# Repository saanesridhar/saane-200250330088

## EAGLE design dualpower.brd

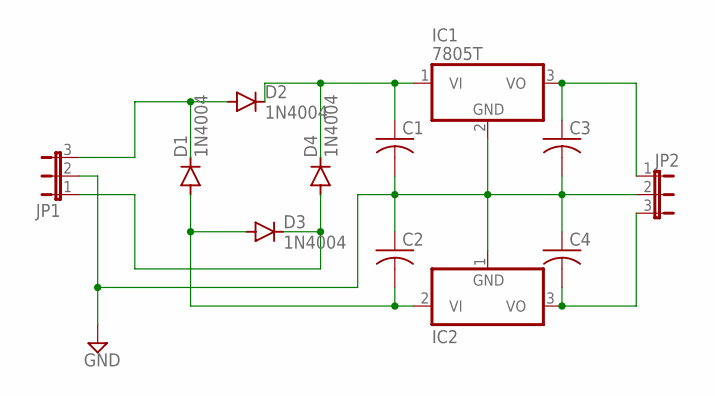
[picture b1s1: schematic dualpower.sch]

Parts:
C1, C2, C3, C4: C-US025-024X044; C025-024X044
D1, D2, D3, D4: 1N4004; DO41-10
IC1: 7805T; TO220H
IC2: 79L05Z; TO92
JP1, JP2: JP2W

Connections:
GND: C1.2, C2.1, C3.2, C4.1, IC1.2 (GND), IC2.1 (GND), JP1.2, JP2.2
unnamed: D1.C, D2.A, JP1.3
unnamed: C2.2, D1.A, D3.A, IC2.2 (VI)
unnamed: D3.C, D4.A, JP1.1
unnamed: C1.1, D2.C, D4.C, IC1.1 (VI)
unnamed: C3.1, IC1.3 (VO), JP2.1
unnamed: C4.2, IC2.3 (VO), JP2.3

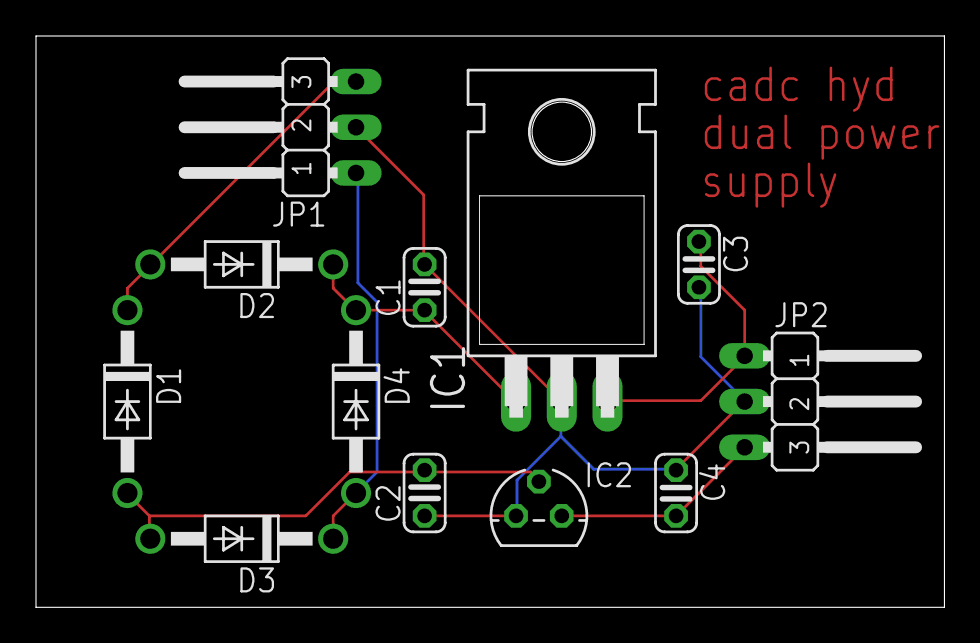
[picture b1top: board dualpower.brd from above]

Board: 2 copper layers, 50.5 x 31.7 mm, 12 parts (0 on the bottom side), 7 nets.

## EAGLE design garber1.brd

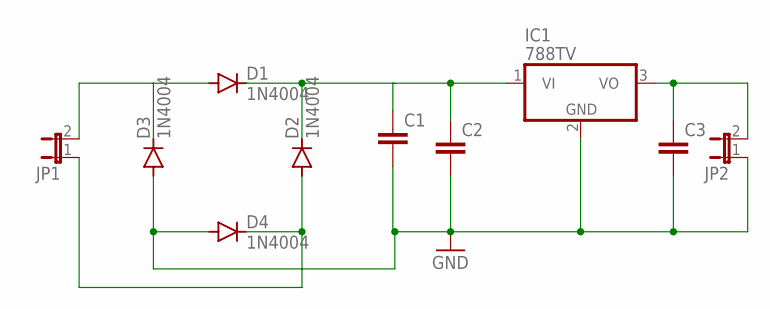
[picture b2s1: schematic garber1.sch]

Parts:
C1, C2, C3: C2,5-3; C2.5-3
D1, D2, D3, D4: 1N4004; DO41-10
IC1: 788TV; TO220V
JP1, JP2: JP1E; JP1

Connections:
GND: C1.2, C2.2, C3.2, D3.A, D4.A, IC1.2 (GND), JP2.1
unnamed: D1.A, D3.C, JP1.2
unnamed: C1.1, C2.1, D1.C, D2.C, IC1.1 (VI)
unnamed: C3.1, IC1.3 (VO), JP2.2
unnamed: D2.A, D4.C, JP1.1

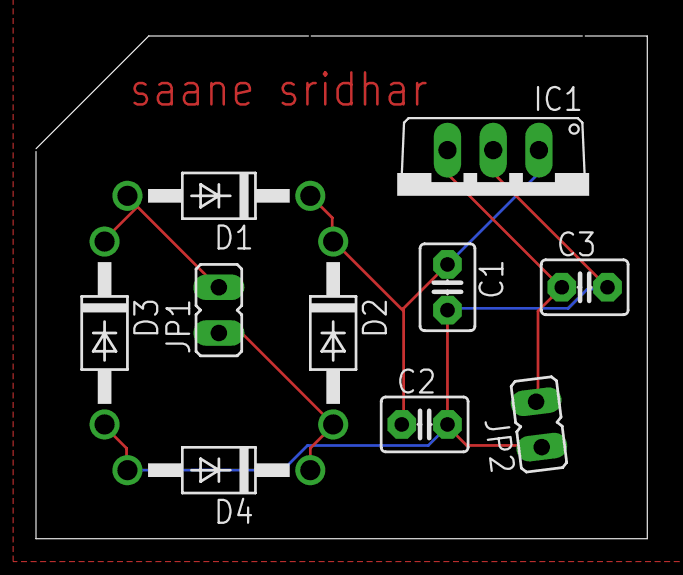
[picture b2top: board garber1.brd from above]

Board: 2 copper layers, 34.0 x 27.9 mm, 10 parts (0 on the bottom side), 5 nets.

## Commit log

2021-02-04 Create rocket
